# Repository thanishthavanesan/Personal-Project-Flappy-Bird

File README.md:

# Personal-Project-Flappy-Bird
A custom-built version of Flappy Bird running entirely on an ESP32 — no game engine, no shortcuts, just hardware. It plays on a small OLED screen, keeps score on a separate 4-digit display (driven through a shift register), and you control it with a joystick plus three buttons for flap, pause, and quit.

Most of the work was in the debugging. The score display flickered until I figured out it needed its own hardware timer running in the background, independent of everything else the chip was doing. Scoring itself was buggy too — it kept missing points because it was checking for one exact pixel position instead of just checking whether the pipe had passed. And the shift register wiring didn't match any online tutorial, so I had to test it pin-by-pin myself to figure out the actual order.

Once the breadboard version worked, I also designed and routed a proper PCB for it in KiCad, going through schematic capture, matching footprints, and cleaning it up until it passed all design checks.

Built with: C/C++ (Arduino), ESP32 (GPIO/ADC/I2C), hardware timers, shift register multiplexing, SSD1306 OLED, KiCad.

** KiCad files are named under "Hobbies" folder and .ino file is named under "ThanishThavanesan_flappy_bird **

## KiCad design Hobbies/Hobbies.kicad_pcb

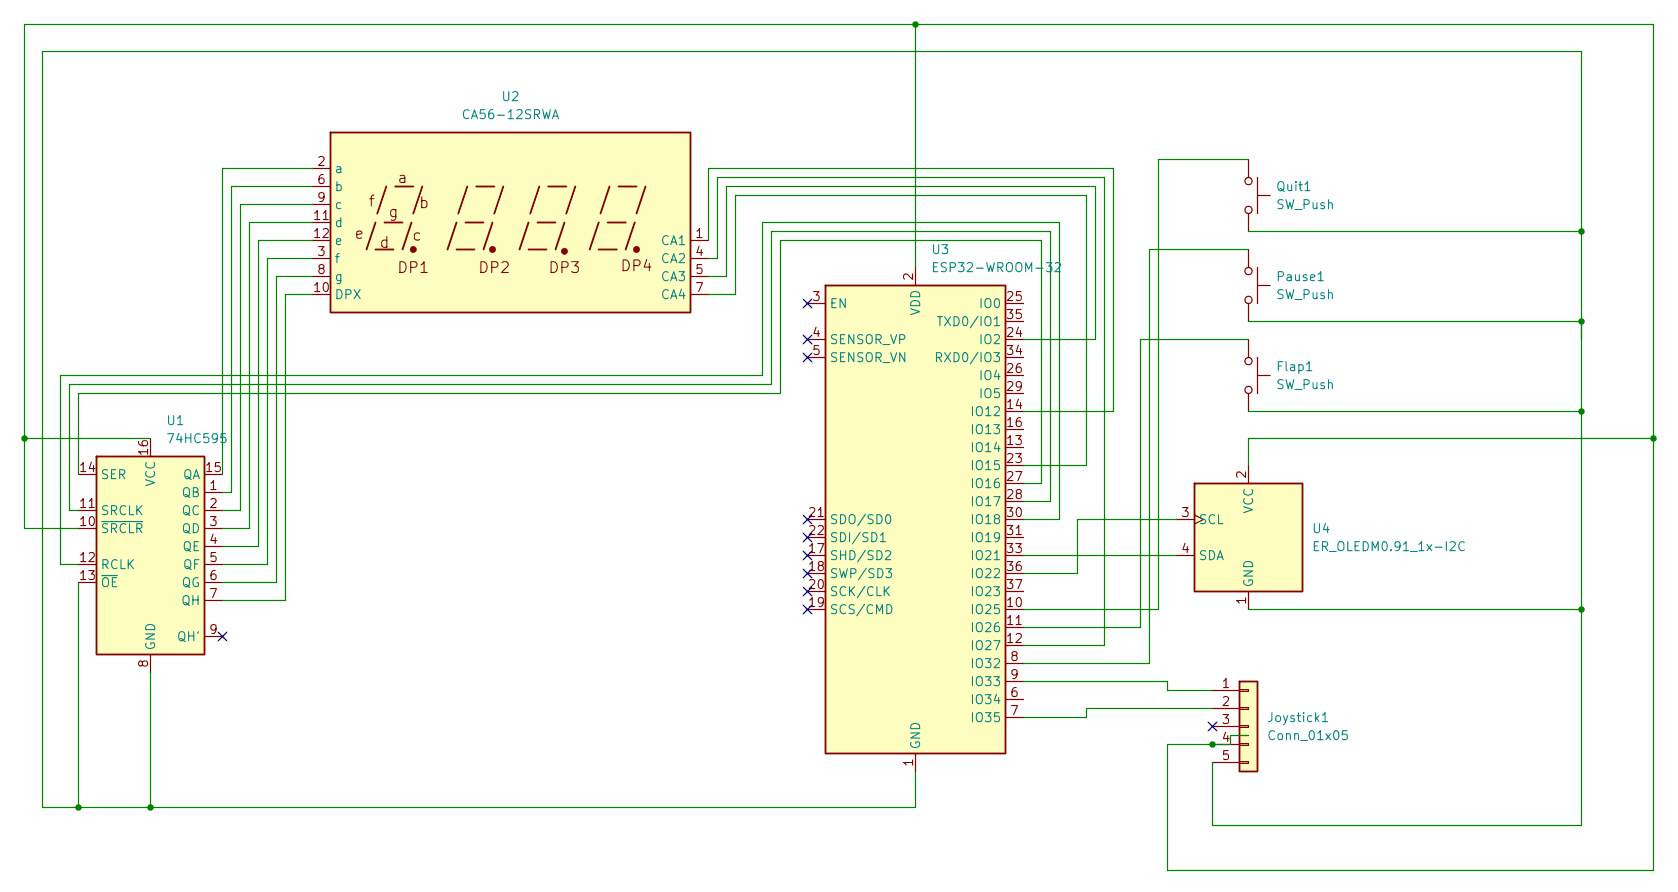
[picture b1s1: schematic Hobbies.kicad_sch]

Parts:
Flap1: SW_Push; SW_PUSH_6mm
Joystick1: Conn_01x05; PinSocket_1x05_P2.54mm_Vertical
Pause1: SW_Push; SW_PUSH_6mm
Quit1: SW_Push; SW_PUSH_6mm
U1: 74HC595; DIP-16_W7.62mm
U2: CA56-12SRWA
U3: ESP32-WROOM-32
U4: ER_OLEDM0.91_1x-I2C; PinSocket_1x04_P2.54mm_Vertical

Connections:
unnamed: Flap1.2, Joystick1.5 (GND), Pause1.2, Quit1.2, U1.8 (GND), U1.13 (~OE), U3.1 (GND), U3.15 (GND), U3.38 (GND), U3.39 (GND), U4.1 (GND)
unnamed: Joystick1.1 (SW), U3.9 (IO33)
unnamed: Joystick1.4 (VCC), U1.10 (~SRCLR), U1.16 (VCC), U3.2 (VDD), U4.2 (VCC)
unnamed: Joystick1.2 (VRy), U3.7 (IO35)
unnamed: U1.15 (QA), U2.2 (a)
unnamed: U1.1 (QB), U2.6 (b)
unnamed: U1.2 (QC), U2.9 (c)
unnamed: U1.3 (QD), U2.11 (d)
unnamed: U1.4 (QE), U2.12 (e)
unnamed: U1.5 (QF), U2.3 (f)
unnamed: U1.6 (QG), U2.8 (g)
unnamed: U1.7 (QH), U2.10 (DPX)
unnamed: U1.12 (RCLK), U3.30 (IO18)
unnamed: U1.14 (SER), U3.27 (IO16)
unnamed: U1.11 (SRCLK), U3.28 (IO17)
unnamed: U2.1 (CA1), U3.14 (IO12)
unnamed: U2.4 (CA2), U3.12 (IO27)
unnamed: U2.5 (CA3), U3.24 (IO2)
unnamed: U2.7 (CA4), U3.23 (IO15)
unnamed: U3.33 (IO21), U4.4 (SDA)
unnamed: U3.36 (IO22), U4.3 (SCL)
unnamed: Quit1.1, U3.10 (IO25)
unnamed: Flap1.1, U3.11 (IO26)
unnamed: Pause1.1, U3.8 (IO32)

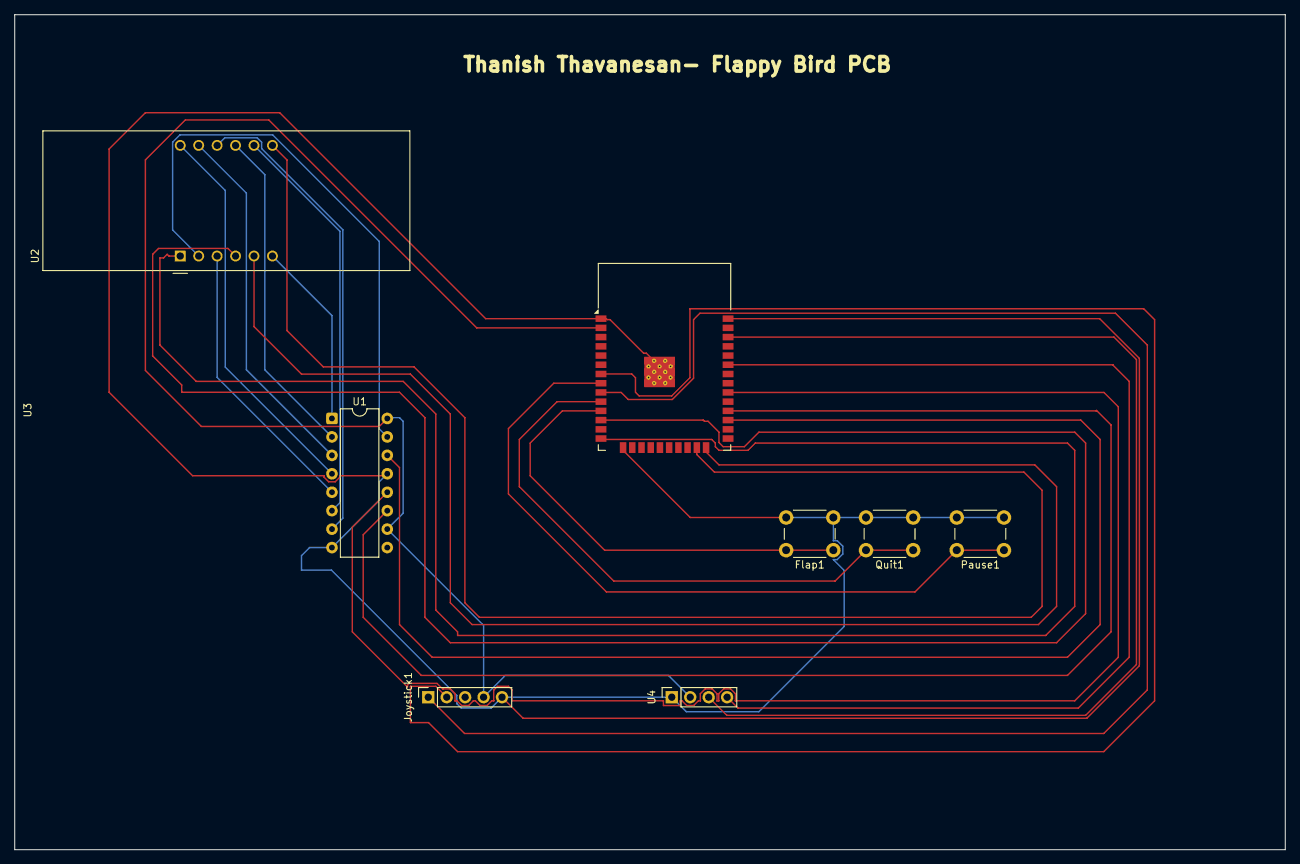
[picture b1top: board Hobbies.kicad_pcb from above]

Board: 2 copper layers, 175.0 x 115.0 mm, 8 parts (0 on the bottom side), 24 nets.
